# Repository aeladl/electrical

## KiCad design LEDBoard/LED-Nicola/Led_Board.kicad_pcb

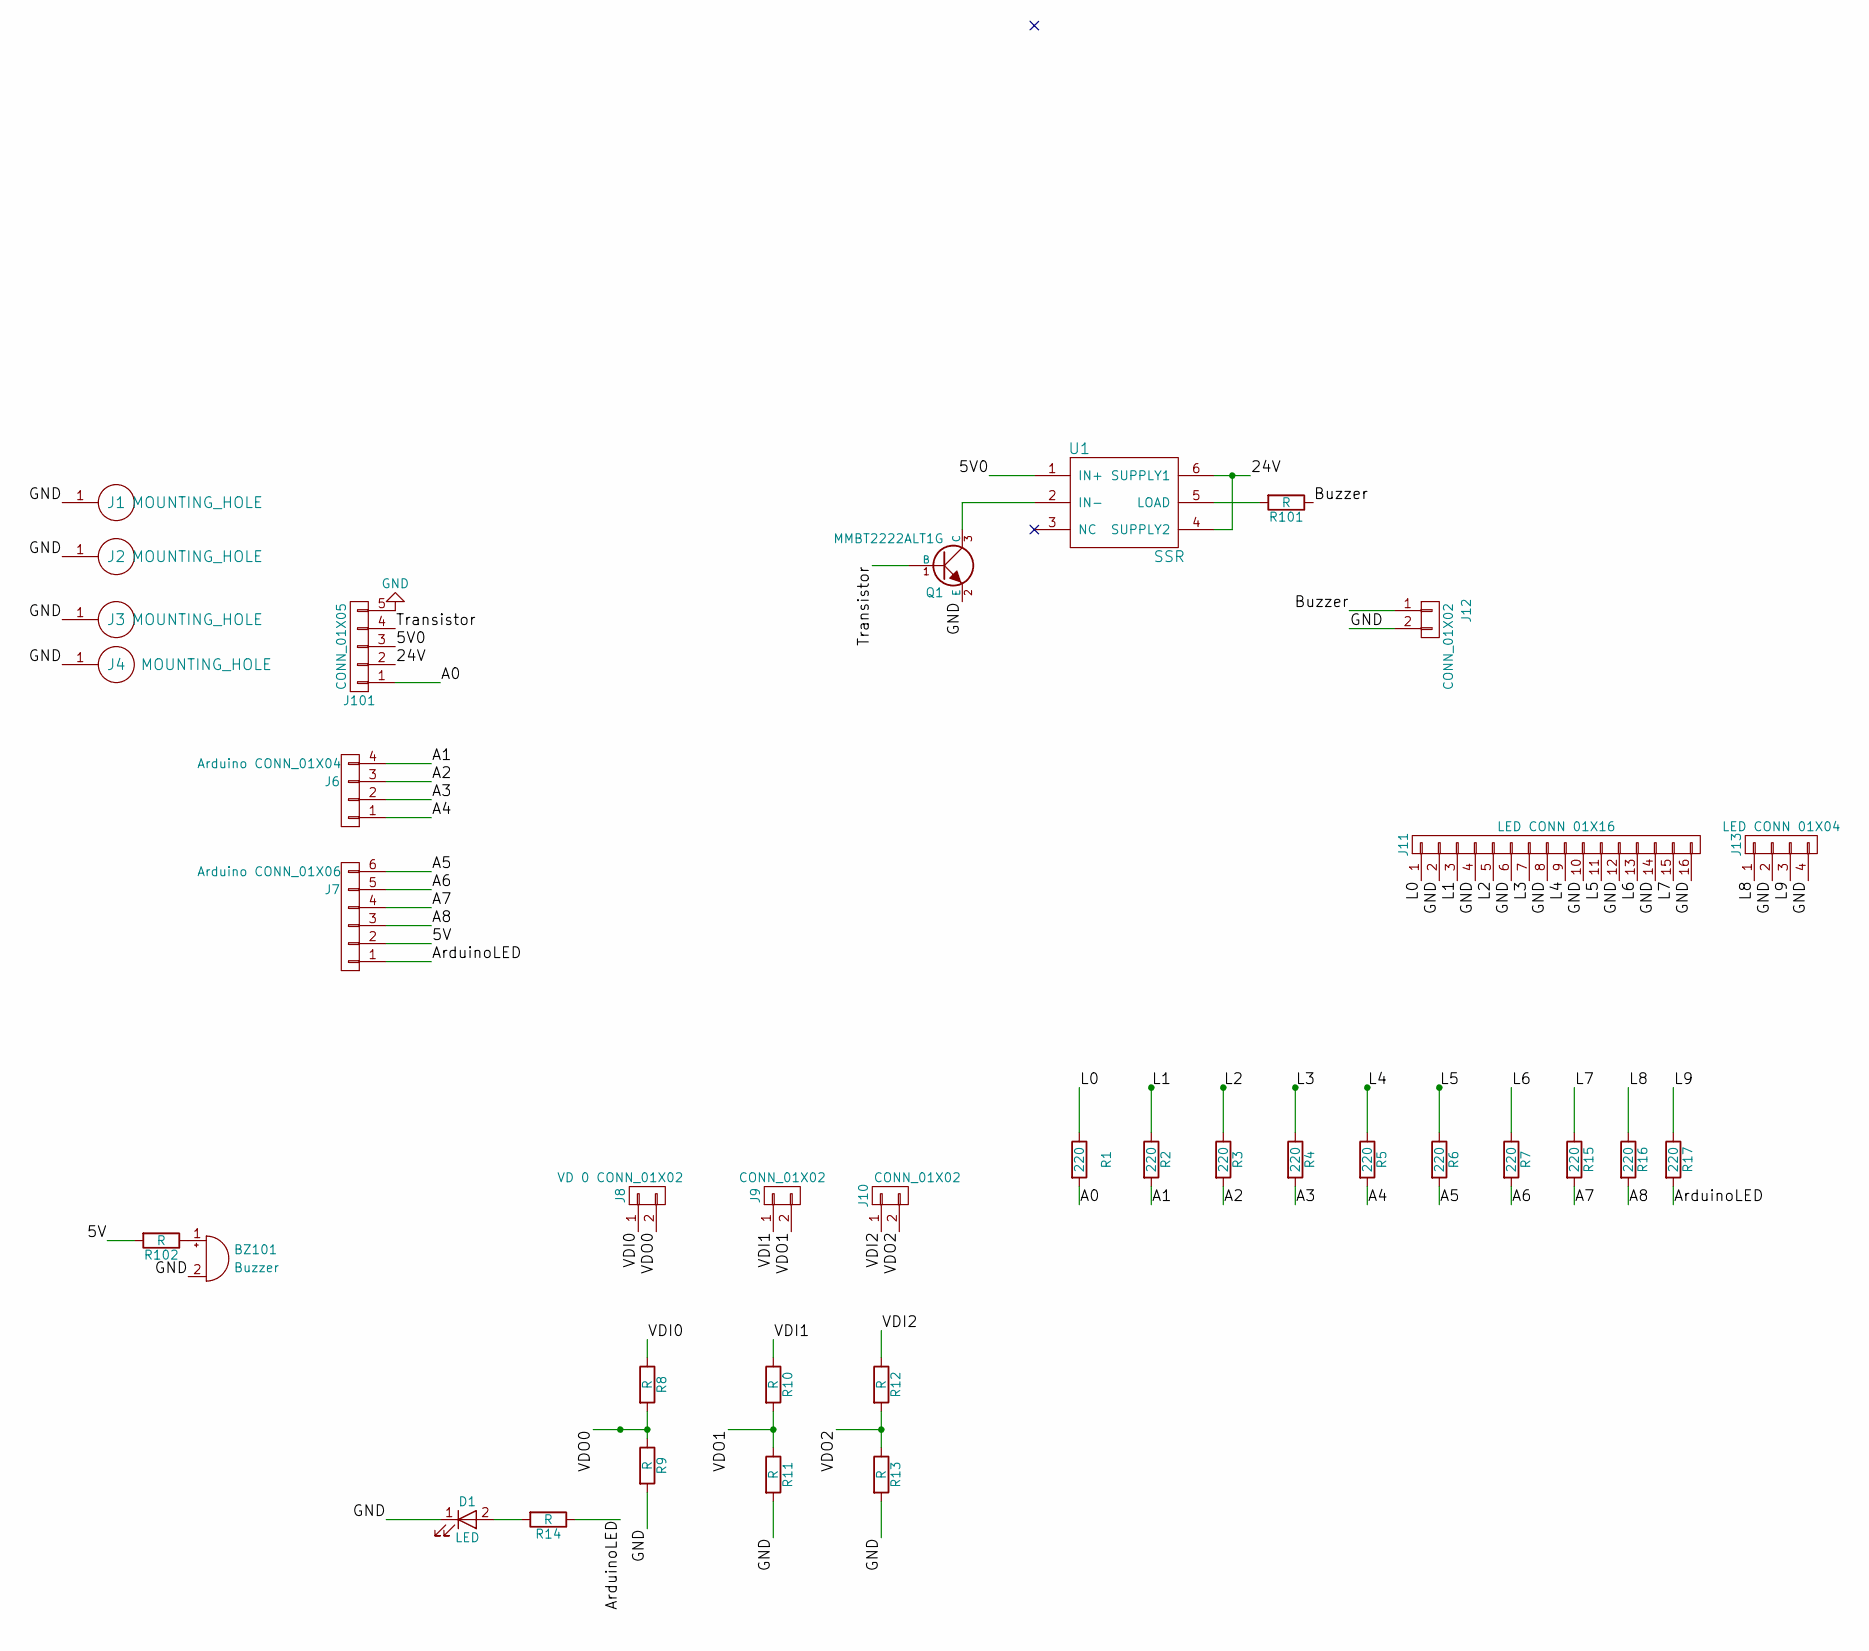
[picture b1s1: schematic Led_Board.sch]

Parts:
BZ101: Buzzer; nicolaBuzzer; Digikey PN 668-1204-ND
D1: LED; D_1206
J1, J2, J3, J4: MOUNTING_HOLE; MountingHole_5.5mm_Pad_Via
J6: Arduino CONN_01X04; CONN_PHOENIX_1844236_4PIN; Mfg. PN 1844236; Digikey PN 277-2419-ND
J7: Arduino CONN_01X06; CONN_PHOENIX_1844252_6PIN; Mfg. PN 1844525; Digikey PN 277-2427-ND
J8: VD 0 CONN_01X02; CONN_PHOENIX_1844210_2PIN; Mfg. PN 1844210; Digikey PN 277-2416-ND
J9, J12: CONN_01X02; CONN_PHOENIX_1844210_2PIN; Mfg. PN 1844210; Digikey PN 277-2416-ND
J10: CONN_01X02; CONN_PHOENIX_1844210_2PIN; Mfg. PN 1844210; DigiKey PN 277-2416-ND
J11: LED CONN 01X16; CONN_PHOENIX_1844359_16PIN; Mfg. PN 1828003; Digikey PN 277-6211-ND
J13: LED CONN 01X04; CONN_PHOENIX_1844236_4PIN; Mfg. PN 1844236; Digikey PN 277-2419-ND
J101: CONN_01X05; CONN_PHOENIX_1844252_5PIN; Digikey PN 277-1610-ND
Q1: MMBT2222ALT1G; MMBF170LT1G
R1, R2, R3, R4, R5, R6, R7, R15, R16, R17: 220; R_1206_HandSoldering
R8, R9, R10, R11, R12, R13, R14: R; R_1206_HandSoldering
R101, R102: R; R_Axial_DIN0309_L9.0mm_D3.2mm_P12.70mm_Horizontal
U1: SSR; SOIC254P1005X390-6N; Mfg. PN VO14642AABTR; Digikey PN VO14642AABCT-ND

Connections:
/5V: J7.2, R102.2
/5V0: J101.3, U1.1 (IN+)
/24V: J101.2, U1.4 (SUPPLY2), U1.6 (SUPPLY1)
/A0: J101.1, R1.2
/A1: J6.4, R2.2
/A2: J6.3, R3.2
/A3: J6.2, R4.2
/A4: J6.1, R5.2
/A5: J7.6, R6.2
/A6: J7.5, R7.2
/A7: J7.4, R15.2
/A8: J7.3, R16.2
/ArduinoLED: J7.1, R14.1, R17.2
/Buzzer: J12.1, R101.1
/L0: J11.1, R1.1
/L1: J11.3, R2.1
/L2: J11.5, R3.1
/L3: J11.7, R4.1
/L4: J11.9, R5.1
/L5: J11.11, R6.1
/L6: J11.13, R7.1
/L7: J11.15, R15.1
/L8: J13.1, R16.1
/L9: J13.3, R17.1
/Transistor: J101.4, Q1.1 (B)
/VDI0: J8.1, R8.1
/VDI1: J9.1, R10.1
/VDI2: J10.1, R12.1
/VDO0: J8.2, R8.2, R9.1
/VDO1: J9.2, R10.2, R11.1
/VDO2: J10.2, R12.2, R13.1
GND: BZ101.2 (+), D1.1 (K), J1.1, J2.1, J3.1, J4.1, J11.2, J11.4, J11.6, J11.8, J11.10, J11.12, J11.14, J11.16, J12.2, J13.2, J13.4, J101.5, Q1.2 (E), R9.2, R11.2, R13.2
unnamed: BZ101.1 (-), R102.1
unnamed: D1.2 (A), R14.2
unnamed: Q1.3 (C), U1.2 (IN-)
unnamed: R101.2, U1.5 (LOAD)

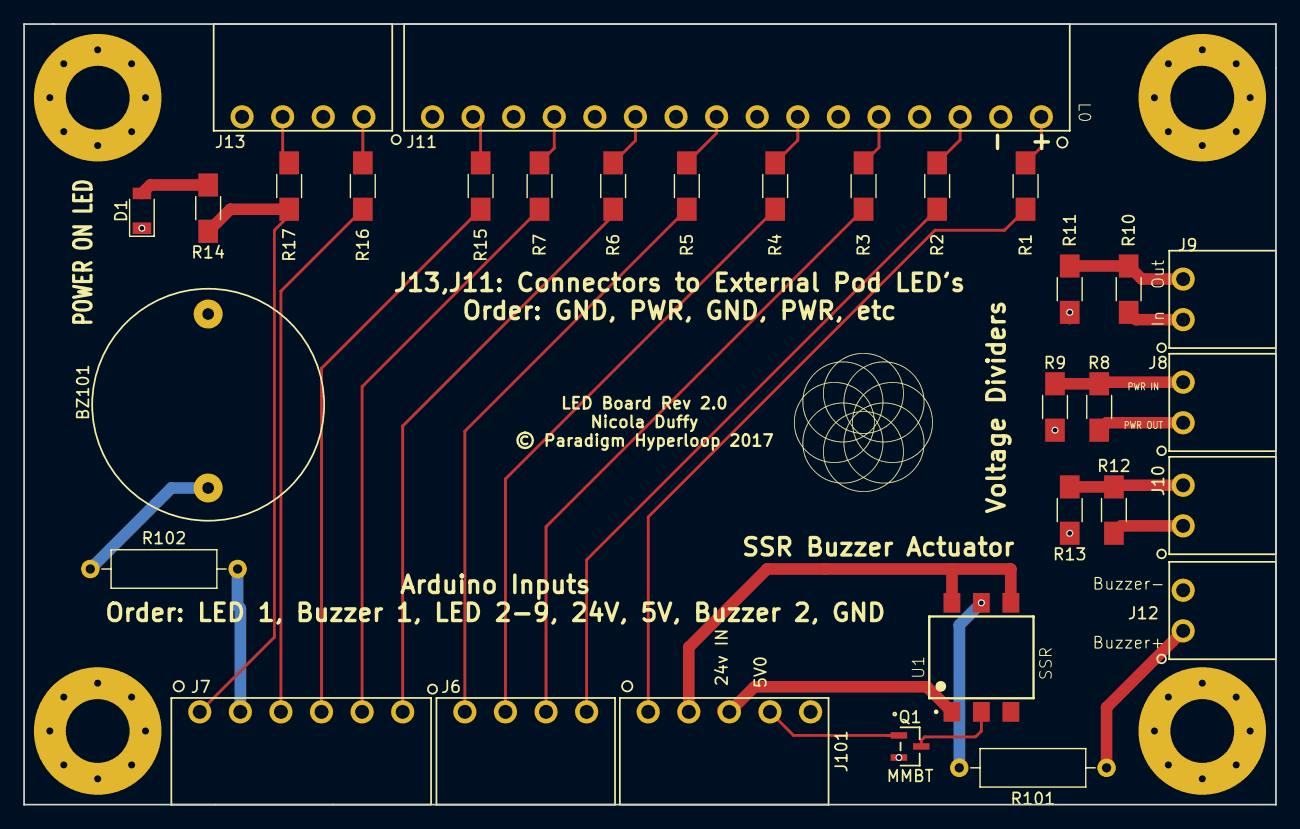
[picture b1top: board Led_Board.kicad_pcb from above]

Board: 2 copper layers, 107.9 x 67.3 mm, 36 parts (0 on the bottom side), 36 nets.

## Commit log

2017-07-30 Changes
    plz let me push
2017-07-31 made changes
2017-07-31 new changes
2017-07-31 Finalized LED Board
    Added Silkscreen for all sides of the board and all connectors. Moved
    the Placement of the Power on LED to show then the arduino is
    outputting power correctly. Slightly move components to make it more
    efficient.
2017-08-01 Made a couple final changes to the LED Board- Should be good to go
2017-08-02 Added Connector
2017-08-02 Final Changes
    Good to go. Added the correct 5 pin connector.
2017-08-02 Added logo
2017-08-02 Final changes
2017-08-02 small silkscreen change - copyright and version location
2017-08-02 Got rid of the unnecessary files

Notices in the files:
LEDBoard/LED-Nicola/Led_Board.kicad_pcb:
© Paradigm Hyperloop 2017
parts and their libraries:
Copyright 2016 Accelerated Designs. All rights reserved.
